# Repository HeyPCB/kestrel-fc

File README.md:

# Kestrel H7: FPV flight controller

**An STM32H743 flight controller for 5-inch 6S quads: two IMUs, a barometer, a 16 MB blackbox and its own 5 V and switchable 10 V BECs, on a 30.5 mm stack.**

The Kestrel H7 is the flight controller of [Kestrel](https://github.com/HeyPCB/kestrel), a 5-inch 6S FPV quad's electronics. Its pin map follows Betaflight's `MATEKH743` target wherever the functions match, so its timer and DMA assignments are proven ones; a Betaflight unified target and CLI defaults are in [`firmware/`](firmware/). The ICM-20602 flies Betaflight, and the BMI088 on its own SPI bus is there for INAV and ArduPilot.

| Layers | Size | Footprints (LCSC parts) | Nets | Connections routed | Routed vias | ERC errors / warnings | DRC errors / warnings / unconnected / parity | Parts per board, 10-board build |
|---|---|---|---|---|---|---|---|---|
| 6 | 40 x 40 mm | 114 (93) | 84 | 277 -> 0 open | 125 | 0 / 0 | 0 / 0 / 0 / 0 | $46.49 |

**Not fabricated, assembled, powered or flown yet.** Every number on this page is measured by KiCad
10.0.6 on the files in this repository ([`report.json`](report.json), [`fab/erc.json`](fab/erc.json),
[`fab/drc.json`](fab/drc.json)) or read from the live JLC/LCSC catalogue ([`bom_cost.md`](bom_cost.md):
parts only, at a 10-board build's price tier with JLC's Extended-part fee; the bare PCB and assembly are
quoted at order time).

| | |
|---|---|
| The whole drone: spec, build guide, BOM, measured results | [HeyPCB/kestrel](https://github.com/HeyPCB/kestrel) |
| KiCad 10 project | [`kicad/`](kicad/) |
| Gerbers, drill, BOM, CPL, STEP, schematic PDF | [`fab/`](fab/) |
| Firmware | [`firmware/betaflight/KESTRELH7/`](firmware/betaflight/KESTRELH7/): Betaflight unified target and CLI defaults |
| Renders | [front](media/top.png), [back](media/bottom.png), [hero](media/hero.png), [Circuit World thumbnail](media/circuit-world.png) |
| Brief and generator | [`design/`](design/) |

## What's on it

- **MCU:** STM32H743VIT6 (LQFP-100, 480 MHz, 2 MB flash), 8 MHz crystal, BOOT button, SWD pads.
- **IMUs:** ICM-20602 on SPI1 with its own interrupt (Betaflight's gyro); BMI088 on SPI4 (INAV and ArduPilot). Both run from their own AP2112K LDO, away from the BECs' switching.
- **Baro:** MS5611 on I2C1 at 0x77 (cover it with open-cell foam).
- **Blackbox:** W25Q128JV, 16 MB, on SPI3.
- **Power:** 2-6S from the ESC harness, SMAJ30A TVS, VBAT x 1/11 to an ADC; a 5 V BEC (LMR51430, 2 A budget) and a 10 V BEC for the VTX that PINIO1 switches off.
- **Ports:** JST-SH ESC 8-pin, VTX 6-pin, receiver 4-pin and GPS 6-pin; USB-C with USBLC6 ESD.
- **Pads:** M5-M8, UART1 and UART6, LED strip, buzzer, 5 V, 10 V, GND (the pad map is in the hub's [BUILD.md](https://github.com/HeyPCB/kestrel/blob/main/BUILD.md)).

## Ordering

6 layers, 1.6 mm, 1 oz copper; parts on both faces. Upload [`fab/kestrel_fc_gerbers.zip`](fab/kestrel_fc_gerbers.zip), [`fab/kestrel_fc_bom.csv`](fab/kestrel_fc_bom.csv)
and [`fab/kestrel_fc_cpl_jlc.csv`](fab/kestrel_fc_cpl_jlc.csv) to JLCPCB: every part has an LCSC number.
Bring-up, one board at a time, is in the hub's [BUILD.md](https://github.com/HeyPCB/kestrel/blob/main/BUILD.md).

## How it was made

Designed with the HeyPCB method on KiCad 10.0.6, headless, by the `heypcb-kicad` pipeline: a written brief composed from reusable circuit blocks, every pin from KiCad's own symbol library, every part bound to an LCSC number from a dated catalogue read, then ERC, a netlist round trip, locked placement, Freerouting 2.4.1, pours and stitching, silkscreen, DRC with schematic parity, DFM and a fab gate, each stage gated by a measurement. [`design/make_brief.py`](design/make_brief.py) regenerates the brief (outline, part locks, net
classes) from code.

Part of [Kestrel](https://github.com/HeyPCB/kestrel), a 5-inch 6S FPV quad's electronics.

## License

Hardware: [CERN-OHL-S v2](LICENSE). The Betaflight target in [`firmware/`](firmware/) is GPL-3.0 ([`firmware/LICENSE`](firmware/LICENSE)), the licence of the betaflight/config repository it builds in, whose `MATEKH743` timer and DMA assignments it reuses. KiCad's symbol, footprint and 3D libraries used in the
design are CC-BY-SA 4.0 with the KiCad library exception.

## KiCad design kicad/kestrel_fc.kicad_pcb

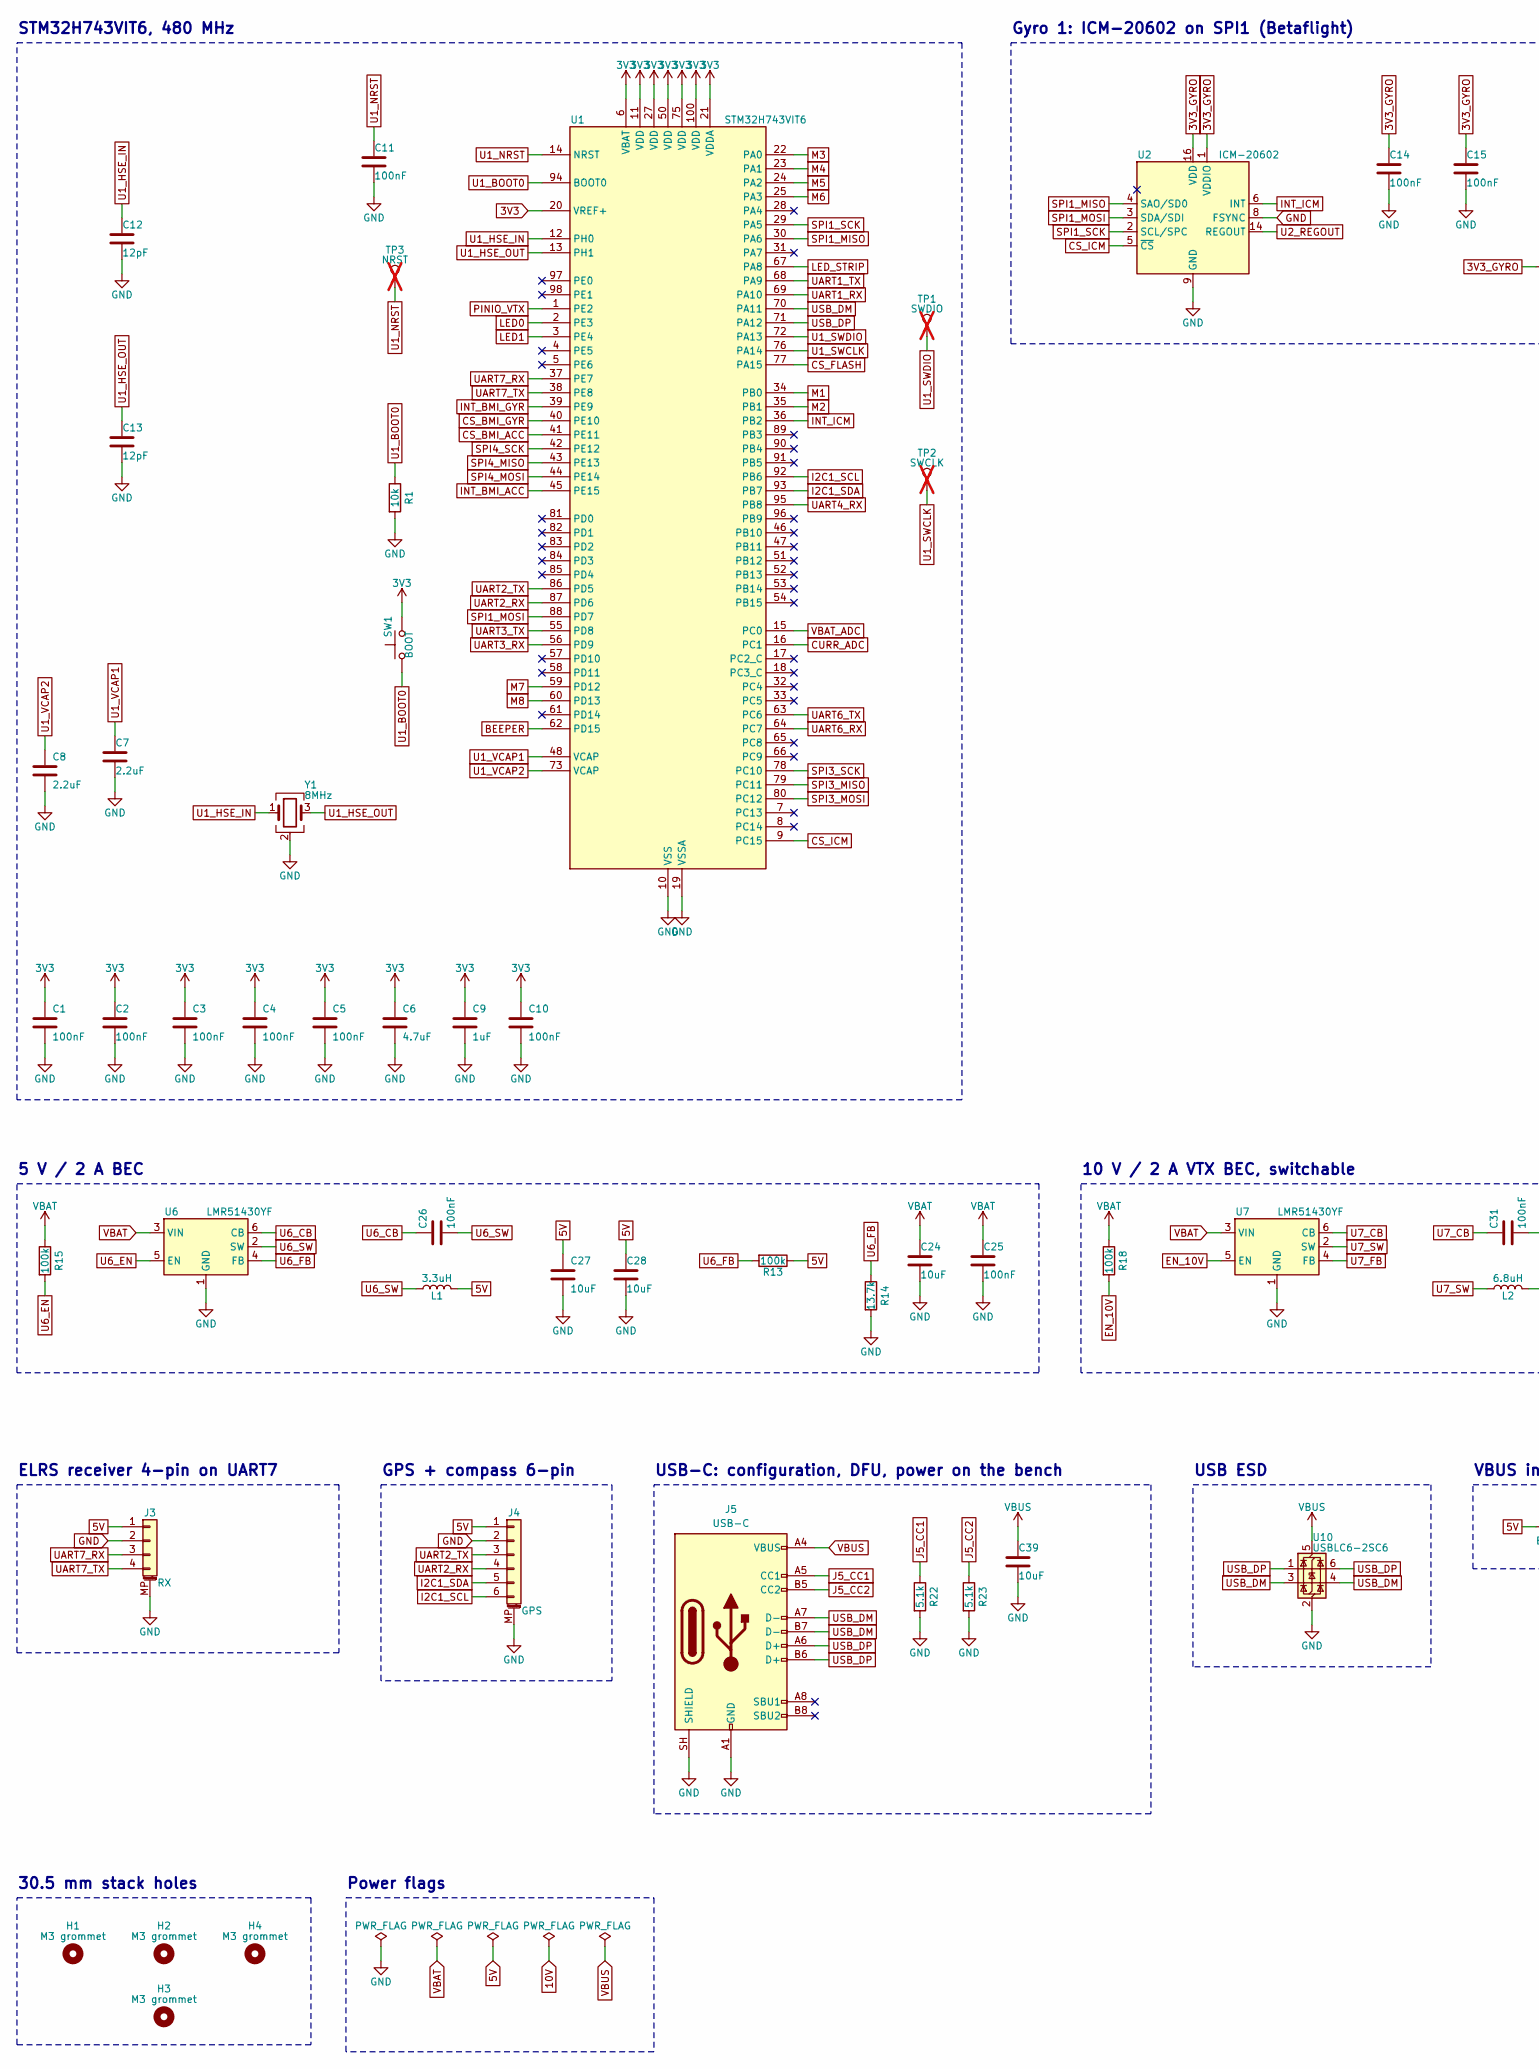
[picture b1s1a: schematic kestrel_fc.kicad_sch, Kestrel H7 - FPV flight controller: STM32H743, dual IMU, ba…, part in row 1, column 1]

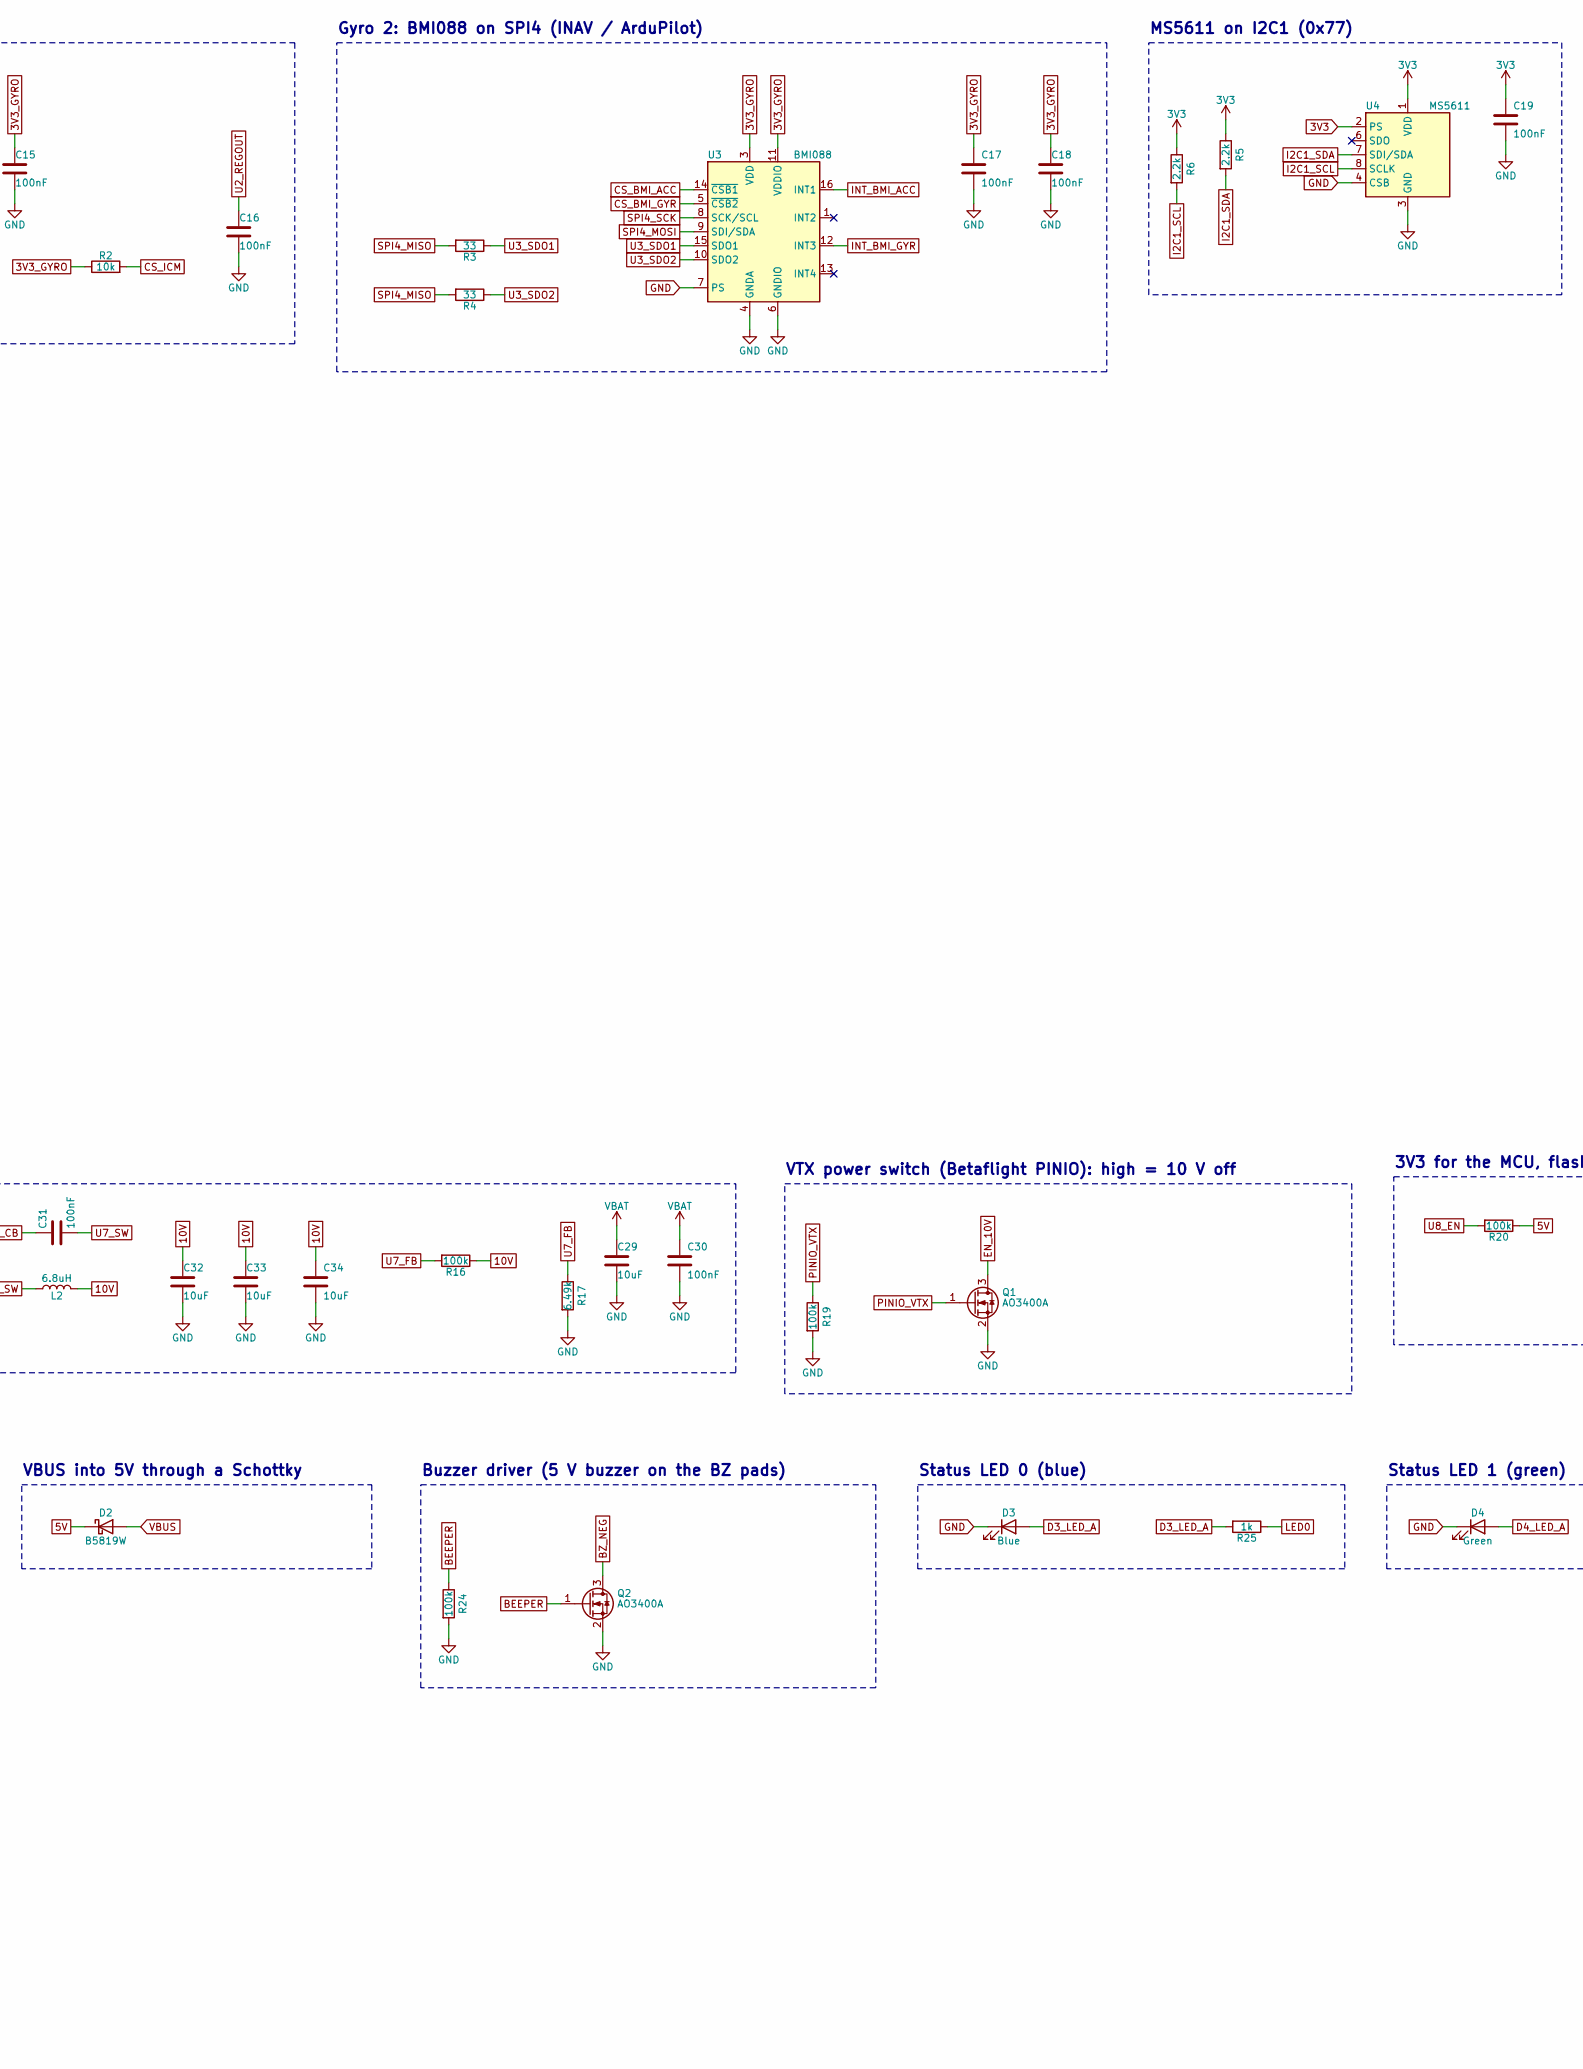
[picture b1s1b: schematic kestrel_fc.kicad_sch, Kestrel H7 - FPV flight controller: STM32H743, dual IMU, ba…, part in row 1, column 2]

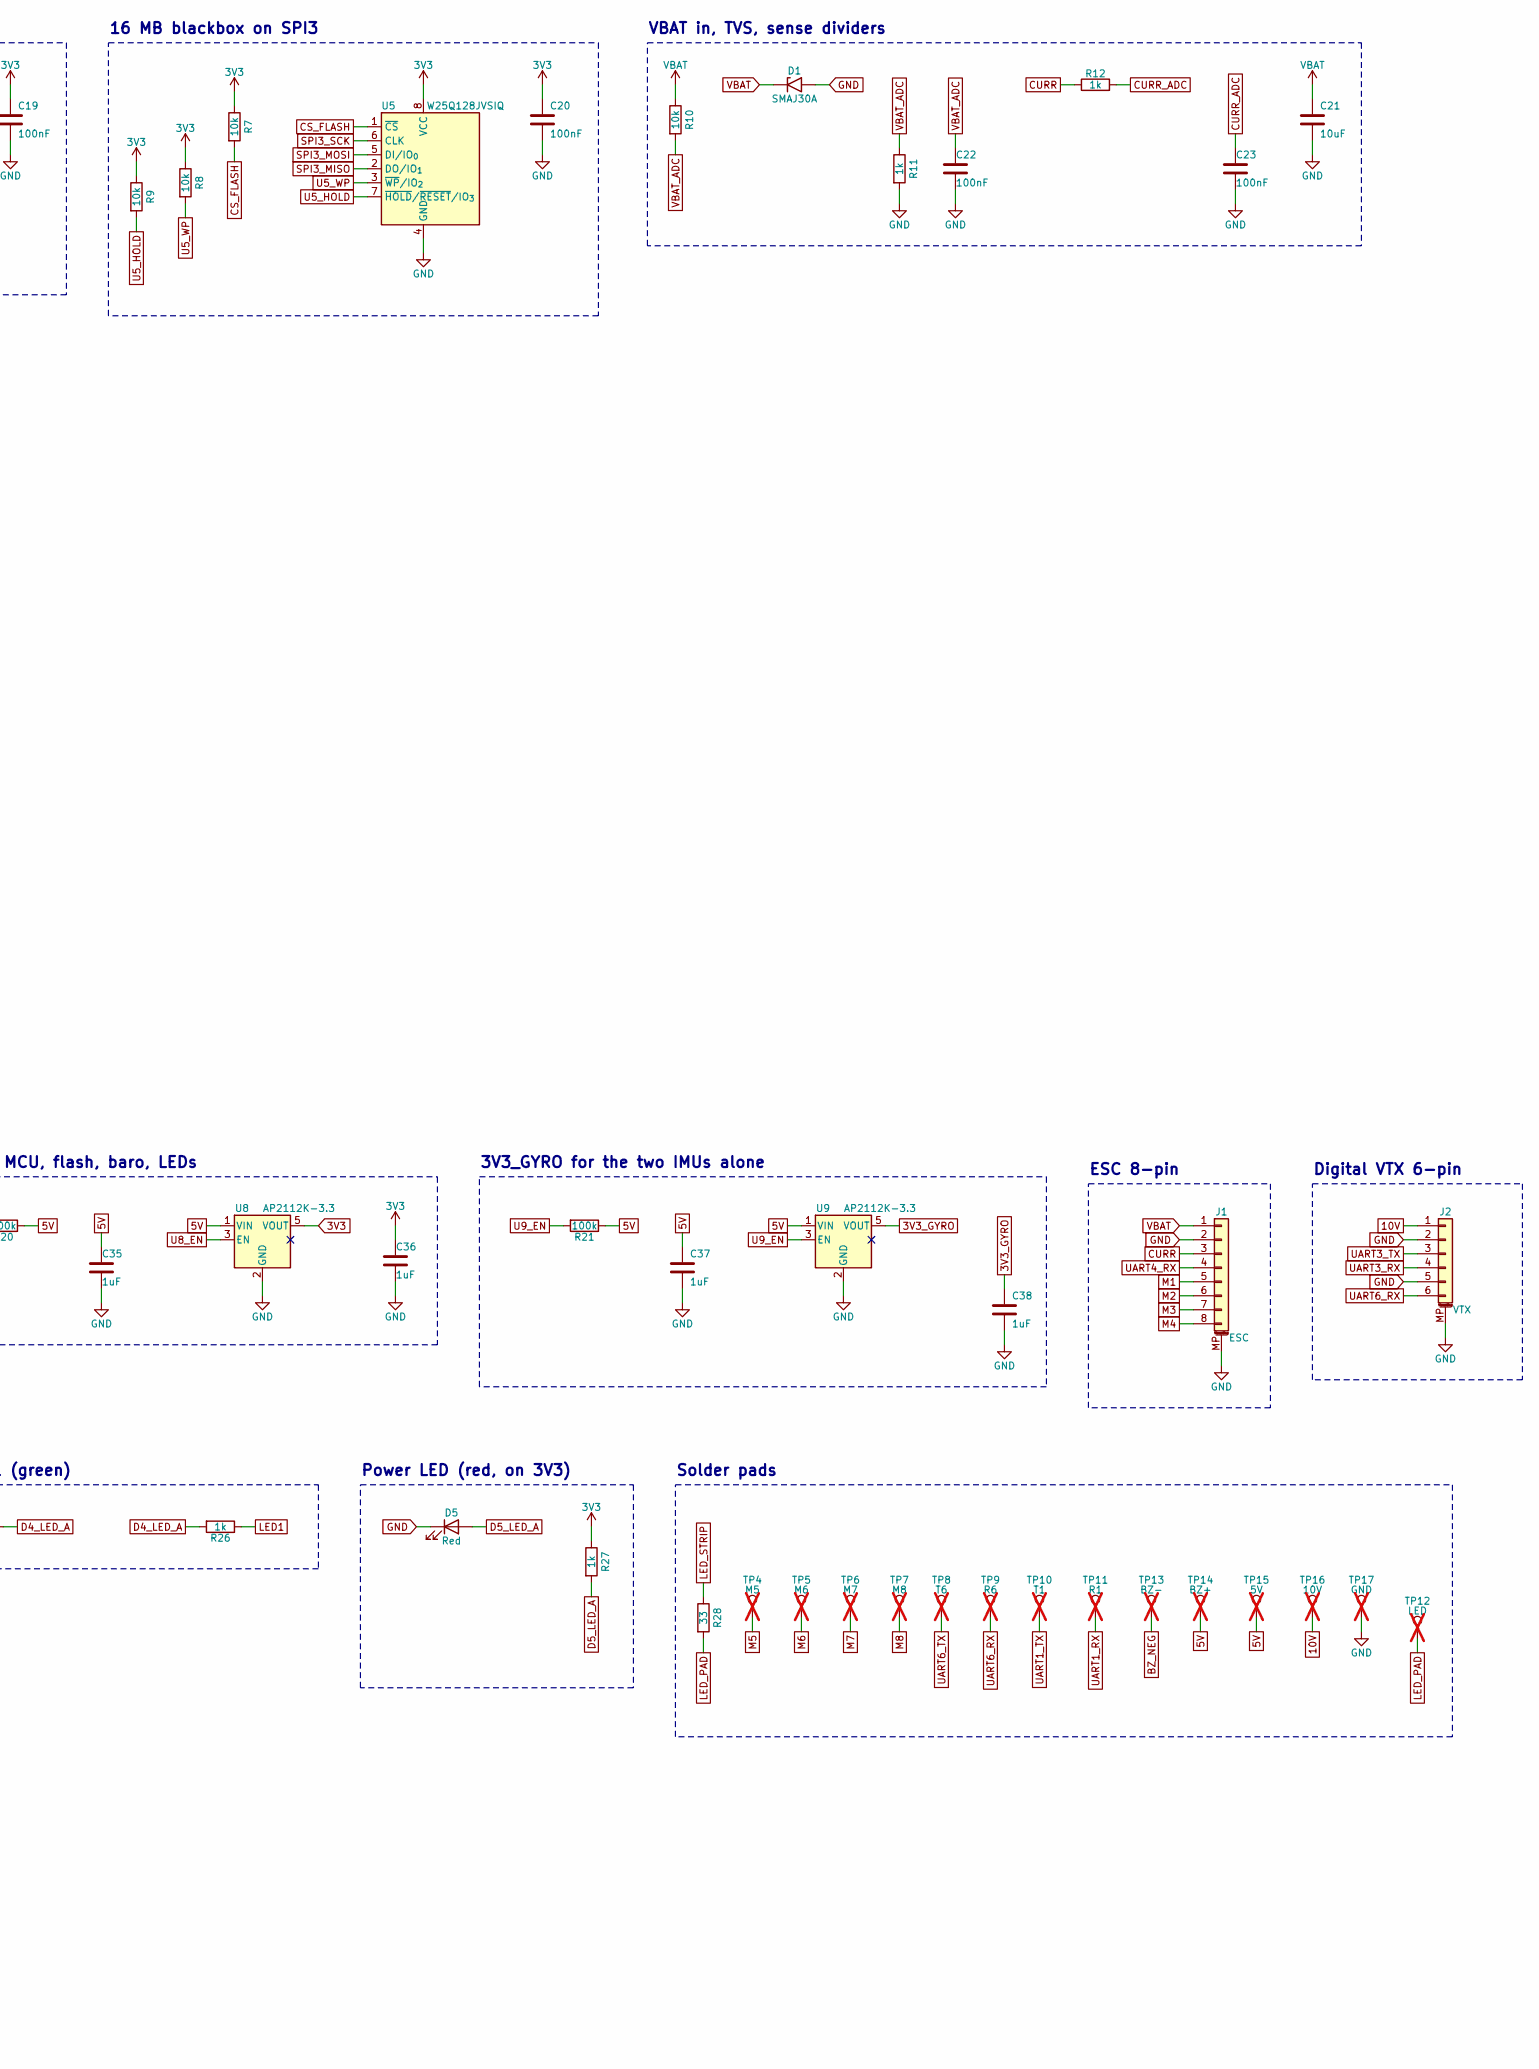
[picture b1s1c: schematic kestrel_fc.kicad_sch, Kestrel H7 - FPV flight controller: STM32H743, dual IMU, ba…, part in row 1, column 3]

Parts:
C1, C2, C3, C4, C5, C10, C11, C14, C15, C16, C17, C18, C19, C20, C22, C23, C26, C31: 100nF; C_0402_1005Metric; MPN CL05B104KO5NNNC; LCSC C1525
C6: 4.7uF; C_0603_1608Metric; MPN CL10A475KO8NNNC; LCSC C19666
C7, C8: 2.2uF; C_0402_1005Metric; MPN CL05A225MQ5NSNC; LCSC C12530
C9, C35, C36, C37, C38: 1uF; C_0402_1005Metric; MPN CL05A105KA5NQNC; LCSC C52923
C12, C13: 12pF; C_0603_1608Metric; MPN CL10C120JB8NNNC; LCSC C38523
C21, C24, C27, C28, C29, C32, C33, C34: 10uF; C_0805_2012Metric; MPN GRM21BR61H106KE43L; LCSC C440198
C25, C30: 100nF; C_0402_1005Metric; MPN CL05B104KB54PNC; LCSC C307331
C39: 10uF; C_0805_2012Metric; MPN CL21A106KAYNNNE; LCSC C15850
D1: SMAJ30A; D_SMA; MPN SMAJ30A; LCSC C908776
D2: B5819W; D_SOD-123; MPN B5819W SL; LCSC C8598
D3: Blue; LED_0603_1608Metric; MPN NCD0603B1; LCSC C84266
D4: Green; LED_0603_1608Metric; MPN KT-0603G; LCSC C12624
D5: Red; LED_0603_1608Metric; MPN KT-0603R; LCSC C2286
H1, H2, H3, H4: M3 grommet; MountingHole_4mm
J1: ESC; JST_SH_SM08B-SRSS-TB_1x08-1MP_P1.00mm_Horizontal; MPN SM08B-SRSS-TB(LF)(SN); LCSC C160407
J2: VTX; JST_SH_SM06B-SRSS-TB_1x06-1MP_P1.00mm_Horizontal; MPN SM06B-SRSS-TB(LF)(SN); LCSC C160405
J3: RX; JST_SH_SM04B-SRSS-TB_1x04-1MP_P1.00mm_Horizontal; MPN SM04B-SRSS-TB(LF)(SN); LCSC C160404
J4: GPS; JST_SH_SM06B-SRSS-TB_1x06-1MP_P1.00mm_Horizontal; MPN SM06B-SRSS-TB(LF)(SN); LCSC C160405
J5: USB-C; USB_C_Receptacle_HCTL_HC-TYPE-C-16P-01A; MPN HC-TYPE-C-16P-01A; LCSC C2894897
L1: 3.3uH; L_Sunlord_SWPA5040S; MPN SWPA5040S3R3MT; LCSC C14656
L2: 6.8uH; L_Sunlord_SWPA5040S; MPN SWPA5040S6R8MT; LCSC C36411
Q1, Q2: AO3400A; SOT-23; MPN AO3400A; LCSC C20917
R1, R2, R7, R8, R9, R10: 10k; R_0402_1005Metric; MPN 0402WGF1002TCE; LCSC C25744
R3, R4, R28: 33; R_0402_1005Metric; MPN 0402WGF330JTCE; LCSC C25105
R5, R6: 2.2k; R_0402_1005Metric; MPN 0402WGF2201TCE; LCSC C25879
R11, R12: 1k; R_0402_1005Metric; MPN 0402WGF1001TCE; LCSC C11702
R13, R15, R16, R18, R19, R24: 100k; R_0603_1608Metric; MPN 0603WAF1003T5E; LCSC C25803
R14: 13.7k; R_0603_1608Metric; MPN 0603WAF1372T5E; LCSC C22793
R17: 6.49k; R_0603_1608Metric; MPN 0603WAF6491T5E; LCSC C23088
R20, R21: 100k; R_0402_1005Metric; MPN 0402WGF1003TCE; LCSC C25741
R22, R23: 5.1k; R_0402_1005Metric; MPN 0402WGF5101TCE; LCSC C25905
R25, R26, R27: 1k; R_0603_1608Metric; MPN 0603WAF1001T5E; LCSC C21190
SW1: BOOT; SW_SPST_B3U-1000P; MPN B3U-1000P; LCSC C231329
TP1: SWDIO; TestPoint_Pad_1.0x1.0mm; not fitted
TP2: SWCLK; TestPoint_Pad_1.0x1.0mm; not fitted
TP3: NRST; TestPoint_Pad_1.0x1.0mm; not fitted
TP4: M5; TestPoint_Pad_1.5x1.5mm; not fitted
TP5: M6; TestPoint_Pad_1.5x1.5mm; not fitted
TP6: M7; TestPoint_Pad_1.5x1.5mm; not fitted
TP7: M8; TestPoint_Pad_1.5x1.5mm; not fitted
TP8: T6; TestPoint_Pad_1.5x1.5mm; not fitted
TP9: R6; TestPoint_Pad_1.5x1.5mm; not fitted
TP10: T1; TestPoint_Pad_1.5x1.5mm; not fitted
TP11: R1; TestPoint_Pad_1.5x1.5mm; not fitted
TP12: LED; TestPoint_Pad_1.5x1.5mm; not fitted
TP13: BZ-; TestPoint_Pad_1.5x1.5mm; not fitted
TP14: BZ+; TestPoint_Pad_1.5x1.5mm; not fitted
TP15: 5V; TestPoint_Pad_1.5x1.5mm; not fitted
TP16: 10V; TestPoint_Pad_1.5x1.5mm; not fitted
TP17: GND; TestPoint_Pad_1.5x1.5mm; not fitted
U1: STM32H743VIT6; LQFP-100_14x14mm_P0.5mm; MPN STM32H743VIT6; LCSC C114409
U2: ICM-20602; LGA-16_3x3mm_P0.5mm_LayoutBorder3x5y; MPN ICM-20602; LCSC C97633
U3: BMI088; Bosch_LGA-16_4.5x3mm_P0.5mm_LayoutBorder7x1y_ClockwisePinNu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; MPN BMI088; LCSC C194919
U4: MS5611; LGA-8_3x5mm_P1.25mm; MPN MS561101BA03-50; LCSC C15639
U5: W25Q128JVSIQ; SOIC-8_5.3x5.3mm_P1.27mm; MPN W25Q128JVSIQ; LCSC C97521
U6, U7: LMR51430YF; SOT-23-6; MPN LMR51430YFDDCR; LCSC C5219261
U8, U9: AP2112K-3.3; SOT-23-5; MPN AP2112K-3.3TRG1; LCSC C51118
U10: USBLC6-2SC6; SOT-23-6; MPN USBLC6-2SC6; LCSC C7519
Y1: 8MHz; Crystal_SMD_3225-4Pin_3.2x2.5mm; MPN TAXM8M4RDBCCT2T; LCSC C400090

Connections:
3V3: C1.1, C2.1, C3.1, C4.1, C5.1, C6.1, C9.1, C10.1, C19.1, C20.1, C36.1, R5.1, R6.1, R7.1, R8.1, R9.1, R27.1, SW1.2, U1.6 (VBAT), U1.11 (VDD), U1.20 (VREF+), U1.21 (VDDA), U1.27 (VDD), U1.50 (VDD), U1.75 (VDD), U1.100 (VDD), U4.1 (VDD), U4.2 (PS), U5.8 (VCC), U8.5 (VOUT)
3V3_GYRO: C14.1, C15.1, C17.1, C18.1, C38.1, R2.1, U2.1 (VDDIO), U2.16 (VDD), U3.3 (VDD), U3.11 (VDDIO), U9.5 (VOUT)
5V: C27.1, C28.1, C35.1, C37.1, D2.1 (K), J3.1, J4.1, L1.2, R13.1, R20.1, R21.1, TP14.1, TP15.1, U8.1 (VIN), U9.1 (VIN)
10V: C32.1, C33.1, C34.1, J2.1, L2.2, R16.1, TP16.1
BEEPER: Q2.1 (G), R24.1, U1.62 (PD15)
BZ_NEG: Q2.3 (D), TP13.1
CS_BMI_ACC: U1.41 (PE11), U3.14 (~CSB1)
CS_BMI_GYR: U1.40 (PE10), U3.5 (~CSB2)
CS_FLASH: R7.2, U1.77 (PA15), U5.1 (~CS)
CS_ICM: R2.2, U1.9 (PC15), U2.5 (~CS)
CURR: J1.3, R12.1
CURR_ADC: C23.1, R12.2, U1.16 (PC1)
D3_LED_A: D3.2 (A), R25.2
D4_LED_A: D4.2 (A), R26.2
D5_LED_A: D5.2 (A), R27.2
EN_10V: Q1.3 (D), R18.2, U7.5 (EN)
GND: C1.2, C2.2, C3.2, C4.2, C5.2, C6.2, C7.2, C8.2, C9.2, C10.2, C11.2, C12.2, C13.2, C14.2, C15.2, C16.2, C17.2, C18.2, C19.2, C20.2, C21.2, C22.2, C23.2, C24.2, C25.2, C27.2, C28.2, C29.2, C30.2, C32.2, C33.2, C34.2, C35.2, C36.2, C37.2, C38.2, C39.2, D1.2 (A2), D3.1 (K), D4.1 (K), D5.1 (K), J1.2, J1.MP (MountPin), J2.2, J2.5, J2.MP (MountPin), J3.2, J3.MP (MountPin), J4.2, J4.MP (MountPin), J5.A1 (GND), J5.A12 (GND), J5.B1 (GND), J5.B12 (GND), J5.SH (SHIELD), Q1.2 (S), Q2.2 (S), R1.2, R11.2, R14.2, R17.2, R19.2, R22.2, R23.2, R24.2, TP17.1, U1.10 (VSS), U1.19 (VSSA), U1.26 (VSS), U1.49 (VSS), U1.74 (VSS), U1.99 (VSS), U2.8 (FSYNC), U2.9 (GND), U2.10 (GND), U2.11 (GND), U2.12 (GND), U2.13 (GND), U2.15 (GND), U3.2 (GNDA), U3.4 (GNDA), U3.6 (GNDIO), U3.7 (PS), U4.3 (GND), U4.4 (CSB), U4.5 (CSB), U5.4 (GND), U6.1 (GND), U7.1 (GND), U8.2 (GND), U9.2 (GND), U10.2 (GND), Y1.2 (G), Y1.4 (G)
I2C1_SCL: J4.6, R6.2, U1.92 (PB6), U4.8 (SCLK)
I2C1_SDA: J4.5, R5.2, U1.93 (PB7), U4.7 (SDI/SDA)
INT_BMI_ACC: U1.45 (PE15), U3.16 (INT1)
INT_BMI_GYR: U1.39 (PE9), U3.12 (INT3)
INT_ICM: U1.36 (PB2), U2.6 (INT)
J5_CC1: J5.A5 (CC1), R22.1
J5_CC2: J5.B5 (CC2), R23.1
LED0: R25.1, U1.2 (PE3)
LED1: R26.1, U1.3 (PE4)
LED_PAD: R28.2, TP12.1
LED_STRIP: R28.1, U1.67 (PA8)
M1: J1.5, U1.34 (PB0)
M2: J1.6, U1.35 (PB1)
M3: J1.7, U1.22 (PA0)
M4: J1.8, U1.23 (PA1)
M5: TP4.1, U1.24 (PA2)
M6: TP5.1, U1.25 (PA3)
M7: TP6.1, U1.59 (PD12)
M8: TP7.1, U1.60 (PD13)
PINIO_VTX: Q1.1 (G), R19.1, U1.1 (PE2)
SPI1_MISO: U1.30 (PA6), U2.4 (SAO/SD0)
SPI1_MOSI: U1.88 (PD7), U2.3 (SDA/SDI)
SPI1_SCK: U1.29 (PA5), U2.2 (SCL/SPC)
SPI3_MISO: U1.79 (PC11), U5.2 (DO/IO_{1})
SPI3_MOSI: U1.80 (PC12), U5.5 (DI/IO_{0})
SPI3_SCK: U1.78 (PC10), U5.6 (CLK)
SPI4_MISO: R3.2, R4.2, U1.43 (PE13)
SPI4_MOSI: U1.44 (PE14), U3.9 (SDI/SDA)
SPI4_SCK: U1.42 (PE12), U3.8 (SCK/SCL)
U1_BOOT0: R1.1, SW1.1, U1.94 (BOOT0)
U1_HSE_IN: C12.1, U1.12 (PH0), Y1.1
U1_HSE_OUT: C13.1, U1.13 (PH1), Y1.3
U1_NRST: C11.1, TP3.1, U1.14 (NRST)
U1_SWCLK: TP2.1, U1.76 (PA14)
U1_SWDIO: TP1.1, U1.72 (PA13)
U1_VCAP1: C7.1, U1.48 (VCAP)
U1_VCAP2: C8.1, U1.73 (VCAP)
U2_REGOUT: C16.1, U2.14 (REGOUT)
U3_SDO1: R3.1, U3.15 (SDO1)
U3_SDO2: R4.1, U3.10 (SDO2)
U5_HOLD: R9.2, U5.7 (~HOLD/~RESET/IO_{3})
U5_WP: R8.2, U5.3 (~WP/IO_{2})
U6_CB: C26.1, U6.6 (CB)
U6_EN: R15.2, U6.5 (EN)
U6_FB: R13.2, R14.1, U6.4 (FB)
U6_SW: C26.2, L1.1, U6.2 (SW)
U7_CB: C31.1, U7.6 (CB)
U7_FB: R16.2, R17.1, U7.4 (FB)
U7_SW: C31.2, L2.1, U7.2 (SW)
U8_EN: R20.2, U8.3 (EN)
U9_EN: R21.2, U9.3 (EN)
UART1_RX: TP11.1, U1.69 (PA10)
UART1_TX: TP10.1, U1.68 (PA9)
UART2_RX: J4.4, U1.87 (PD6)
UART2_TX: J4.3, U1.86 (PD5)
UART3_RX: J2.4, U1.56 (PD9)
UART3_TX: J2.3, U1.55 (PD8)
UART4_RX: J1.4, U1.95 (PB8)
UART6_RX: J2.6, TP9.1, U1.64 (PC7)
UART6_TX: TP8.1, U1.63 (PC6)
UART7_RX: J3.3, U1.37 (PE7)
UART7_TX: J3.4, U1.38 (PE8)
USB_DM: J5.A7 (D-), J5.B7 (D-), U1.70 (PA11), U10.3 (I/O2), U10.4 (I/O2)
USB_DP: J5.A6 (D+), J5.B6 (D+), U1.71 (PA12), U10.1 (I/O1), U10.6 (I/O1)
VBAT: C21.1, C24.1, C25.1, C29.1, C30.1, D1.1 (A1), J1.1, R10.1, R15.1, R18.1, U6.3 (VIN), U7.3 (VIN)
VBAT_ADC: C22.1, R10.2, R11.1, U1.15 (PC0)
VBUS: C39.1, D2.2 (A), J5.A4 (VBUS), J5.A9 (VBUS), J5.B4 (VBUS), J5.B9 (VBUS), U10.5 (VBUS)

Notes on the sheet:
STM32H743VIT6, 480 MHz
Gyro 1: ICM-20602 on SPI1 (Betaflight)
Gyro 2: BMI088 on SPI4 (INAV / ArduPilot)
MS5611 on I2C1 (0x77)
16 MB blackbox on SPI3
VBAT in, TVS, sense dividers
5 V / 2 A BEC
10 V / 2 A VTX BEC, switchable
VTX power switch (Betaflight PINIO): high = 10 V off
3V3 for the MCU, flash, baro, LEDs
3V3_GYRO for the two IMUs alone
ESC 8-pin
Digital VTX 6-pin
ELRS receiver 4-pin on UART7
GPS + compass 6-pin
USB-C: configuration, DFU, power on the bench
USB ESD
VBUS into 5V through a Schottky
Buzzer driver (5 V buzzer on the BZ pads)
Status LED 0 (blue)
Status LED 1 (green)
Power LED (red, on 3V3)
Solder pads
30.5 mm stack holes
Power flags

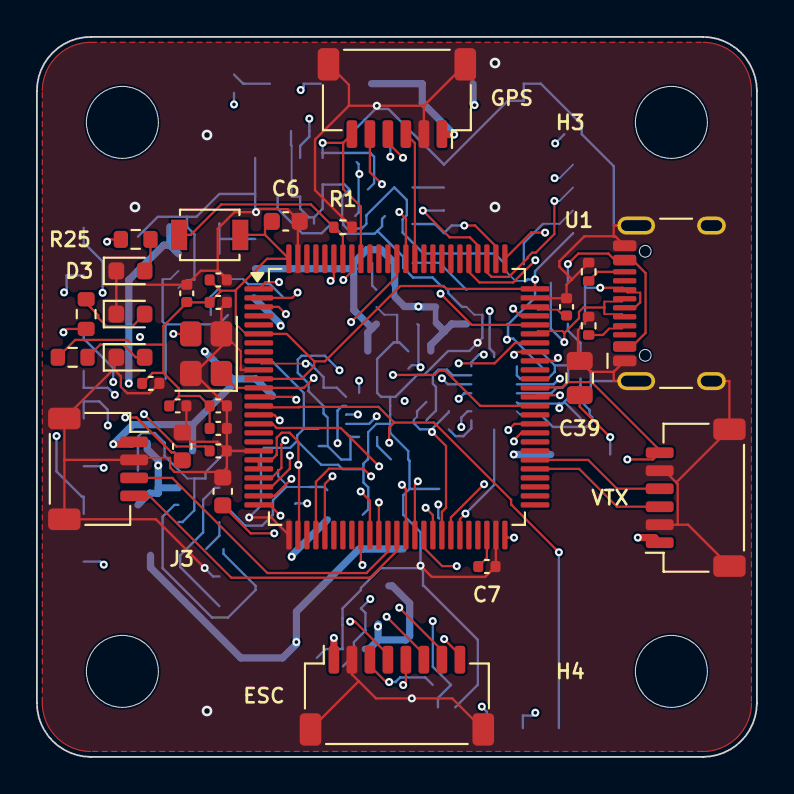
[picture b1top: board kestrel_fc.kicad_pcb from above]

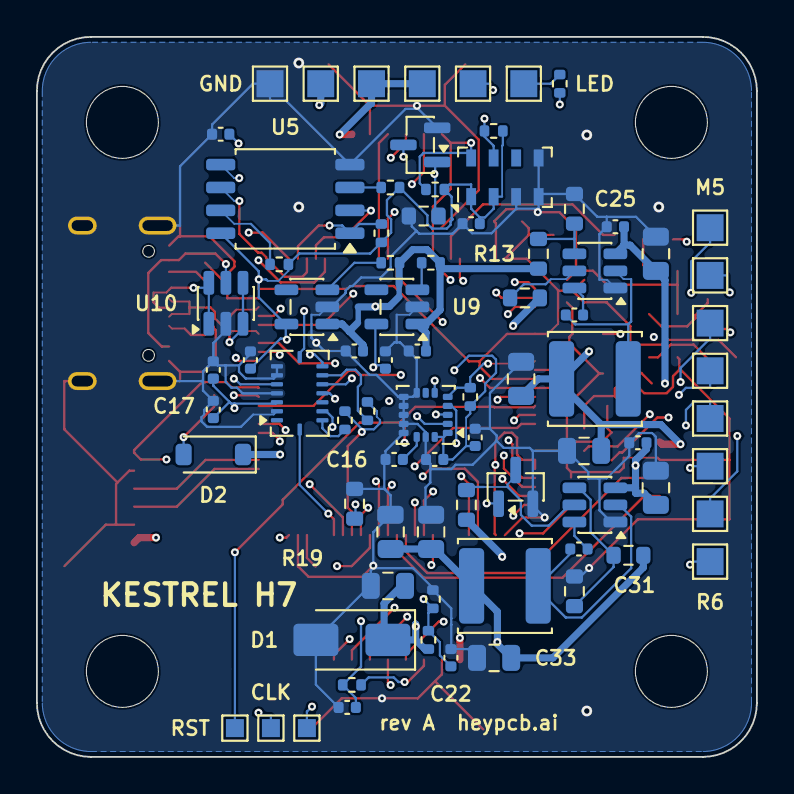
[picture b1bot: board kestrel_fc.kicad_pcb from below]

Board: 6 copper layers, 40.0 x 40.0 mm, 114 parts (79 on the bottom side), 84 nets.

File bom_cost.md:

| Refs | Value | Qty | LCSC | MPN | Class | Unit @10 | Line |
|---|---|---|---|---|---|---|---|
| C1,C2,C3,C4,C5,C10,C11,C14,C15,C16,C17,C18,C19,C20,C22,C23,C26,C31 | 100nF | 18 | C1525 | CL05B104KO5NNNC | basic | $0.0060 | $0.1080 |
| C6 | 4.7uF | 1 | C19666 | CL10A475KO8NNNC | basic | $0.0236 | $0.0236 |
| C7,C8 | 2.2uF | 2 | C12530 | CL05A225MQ5NSNC | basic | $0.0078 | $0.0156 |
| C9,C35,C36,C37,C38 | 1uF | 5 | C52923 | CL05A105KA5NQNC | basic | $0.0143 | $0.0715 |
| C12,C13 | 12pF | 2 | C38523 | CL10C120JB8NNNC | basic | $0.0081 | $0.0162 |
| C21,C24,C27,C28,C29,C32,C33,C34 | 10uF | 8 | C440198 | GRM21BR61H106KE43L | basic | $0.2473 | $1.9784 |
| C25,C30 | 100nF | 2 | C307331 | CL05B104KB54PNC | basic | $0.0076 | $0.0152 |
| C39 | 10uF | 1 | C15850 | CL21A106KAYNNNE | basic | $0.0773 | $0.0773 |
| D1 | SMAJ30A | 1 | C908776 | SMAJ30A | extended | $0.0349 | $0.0349 |
| D2 | B5819W | 1 | C8598 | B5819W SL | basic | $0.0261 | $0.0261 |
| D3 | Blue | 1 | C84266 | NCD0603B1 | extended | $0.0170 | $0.0170 |
| D4 | Green | 1 | C12624 | KT-0603G | extended | $0.0122 | $0.0122 |
| D5 | Red | 1 | C2286 | KT-0603R | basic | $0.0073 | $0.0073 |
| J1 | ESC | 1 | C160407 | SM08B-SRSS-TB(LF)(SN) | extended | $0.3188 | $0.3188 |
| J2 | VTX | 1 | C160405 | SM06B-SRSS-TB(LF)(SN) | extended | $0.3020 | $0.3020 |
| J3 | RX | 1 | C160404 | SM04B-SRSS-TB(LF)(SN) | extended | $0.2262 | $0.2262 |
| J4 | GPS | 1 | C160405 | SM06B-SRSS-TB(LF)(SN) | extended | $0.3020 | $0.3020 |
| J5 | USB-C | 1 | C2894897 | HC-TYPE-C-16P-01A | extended | $0.0998 | $0.0998 |
| L1 | 3.3uH | 1 | C14656 | SWPA5040S3R3MT | extended | $0.0783 | $0.0783 |
| L2 | 6.8uH | 1 | C36411 | SWPA5040S6R8MT | extended | $0.0803 | $0.0803 |
| Q1,Q2 | AO3400A | 2 | C20917 | AO3400A | basic | $0.0846 | $0.1692 |
| R1,R2,R7,R8,R9,R10 | 10k | 6 | C25744 | 0402WGF1002TCE | basic | $0.0029 | $0.0174 |
| R3,R4,R28 | 33 | 3 | C25105 | 0402WGF330JTCE | basic | $0.0010 | $0.0030 |
| R5,R6 | 2.2k | 2 | C25879 | 0402WGF2201TCE | basic | $0.0010 | $0.0020 |
| R11,R12 | 1k | 2 | C11702 | 0402WGF1001TCE | basic | $0.0011 | $0.0022 |
| R13,R15,R16,R18,R19,R24 | 100k | 6 | C25803 | 0603WAF1003T5E | basic | $0.0016 | $0.0096 |
| R14 | 13.7k | 1 | C22793 | 0603WAF1372T5E | extended | $0.0021 | $0.0021 |
| R17 | 6.49k | 1 | C23088 | 0603WAF6491T5E | extended | $0.0013 | $0.0013 |
| R20,R21 | 100k | 2 | C25741 | 0402WGF1003TCE | basic | $0.0040 | $0.0080 |
| R22,R23 | 5.1k | 2 | C25905 | 0402WGF5101TCE | basic | $0.0009 | $0.0018 |
| R25,R26,R27 | 1k | 3 | C21190 | 0603WAF1001T5E | basic | $0.0039 | $0.0117 |
| SW1 | BOOT | 1 | C231329 | B3U-1000P | extended | $0.1784 | $0.1784 |
| U1 | STM32H743VIT6 | 1 | C114409 | STM32H743VIT6 | extended | $8.3101 | $8.3101 |
| U2 | ICM-20602 | 1 | C97633 | ICM-20602 | extended | $6.2635 | $6.2635 |
| U3 | BMI088 | 1 | C194919 | BMI088 | extended | $11.3230 | $11.3230 |
| U4 | MS5611 | 1 | C15639 | MS561101BA03-50 | extended | $6.2798 | $6.2798 |
| U5 | W25Q128JVSIQ | 1 | C97521 | W25Q128JVSIQ | basic | $2.1231 | $2.1231 |
| U6,U7 | LMR51430YF | 2 | C5219261 | LMR51430YFDDCR | extended | $0.6718 | $1.3436 |
| U8,U9 | AP2112K-3.3 | 2 | C51118 | AP2112K-3.3TRG1 | extended | $0.1577 | $0.3154 |
| U10 | USBLC6-2SC6 | 1 | C7519 | USBLC6-2SC6 | extended | $0.1639 | $0.1639 |
| Y1 | 8MHz | 1 | C400090 | TAXM8M4RDBCCT2T | extended | $0.1458 | $0.1458 |
| | **Parts** | | | | | | **$40.49** |
| | Extended-part loading fee ($3 x 20 / 10 boards) | | | | | | $6.00 |
| | **BOM per board @10** | | | | | | **$46.49** |

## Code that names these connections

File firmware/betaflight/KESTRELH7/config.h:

/*
 * Kestrel H7 - Betaflight unified target (config.h for the betaflight/config repository, 4.5+).
 *
 * Every pin below is the net the board's brief puts on that MCU pin (design/make_brief.py,
 * MCU_PINS), named from the KiCad 10 MCU_ST_STM32H7:STM32H743VITx symbol. The motor, LED-strip, UART,
 * I2C1, SPI1, SPI4 and ADC pins are the ones MATEKH743 ships with (configs/MTKS/MATEKH743/config.h,
 * read 2026-10-05), so their timer and DMA assignments below are that target's, unchanged.
 *
 * Not in Betaflight: the BMI088 (gyro 2, SPI4, CS PE11 / PE10) has no Betaflight driver; it is the
 * second IMU for INAV and ArduPilot. Betaflight flies on the ICM-20602 alone.
 *
 * Build:  make CONFIG=KESTRELH7   (with this directory copied to configs/KESTRELH7 of betaflight/config)
 */

#pragma once

#define FC_TARGET_MCU     STM32H743

#define BOARD_NAME        KESTRELH7
#define MANUFACTURER_ID   HYPB

#define USE_ACC
#define USE_ACC_SPI_MPU6500         // ICM-20602 is read by the MPU6500 driver family
#define USE_GYRO
#define USE_GYRO_SPI_MPU6500
#define USE_BARO
#define USE_BARO_MS5611           // I2C1 at 0x77
#define USE_MAG
#define USE_MAG_LIS3MDL             // Kestrel GPS board's compass, I2C1 at 0x1E
#define USE_FLASH
#define USE_FLASH_W25Q128FV
#define USE_GPS

#define BEEPER_PIN           PD15
#define MOTOR1_PIN           PB0
#define MOTOR2_PIN           PB1
#define MOTOR3_PIN           PA0
#define MOTOR4_PIN           PA1
#define MOTOR5_PIN           PA2
#define MOTOR6_PIN           PA3
#define MOTOR7_PIN           PD12
#define MOTOR8_PIN           PD13
#define LED_STRIP_PIN        PA8
#define UART1_TX_PIN         PA9
#define UART2_TX_PIN         PD5
#define UART3_TX_PIN         PD8
#define UART6_TX_PIN         PC6
#define UART7_TX_PIN         PE8
#define UART1_RX_PIN         PA10
#define UART2_RX_PIN         PD6
#define UART3_RX_PIN         PD9
#define UART4_RX_PIN         PB8      // ESC telemetry in (the 4-in-1's TLM wire)
#define UART6_RX_PIN         PC7
#define UART7_RX_PIN         PE7
#define I2C1_SCL_PIN         PB6
#define I2C1_SDA_PIN         PB7
#define LED0_PIN             PE3
#define LED1_PIN             PE4
#define SPI1_SCK_PIN         PA5
#define SPI3_SCK_PIN         PC10
#define SPI4_SCK_PIN         PE12
#define SPI1_SDI_PIN         PA6
#define SPI3_SDI_PIN         PC11
#define SPI4_SDI_PIN         PE13
#define SPI1_SDO_PIN         PD7
#define SPI3_SDO_PIN         PC12
#define SPI4_SDO_PIN         PE14
#define ADC_VBAT_PIN         PC0
#define ADC_CURR_PIN         PC1
#define PINIO1_PIN           PE2      // high switches the 10 V VTX rail off
#define FLASH_CS_PIN         PA15
#define GYRO_1_EXTI_PIN      PB2
#define GYRO_1_CS_PIN        PC15

#define TIMER_PIN_MAPPING \
    TIMER_PIN_MAP( 0, PB0 , 2,  0) \
    TIMER_PIN_MAP( 1, PB1 , 2,  1) \
    TIMER_PIN_MAP( 2, PA0 , 2,  2) \
    TIMER_PIN_MAP( 3, PA1 , 2,  3) \
    TIMER_PIN_MAP( 4, PA2 , 2,  4) \
    TIMER_PIN_MAP( 5, PA3 , 2,  5) \
    TIMER_PIN_MAP( 6, PD12, 1,  6) \
    TIMER_PIN_MAP( 7, PD13, 1,  7) \
    TIMER_PIN_MAP( 8, PA8 , 1,  8)

#define ADC1_DMA_OPT        9
#define TIMUP3_DMA_OPT      11
#define TIMUP4_DMA_OPT      12
#define TIMUP5_DMA_OPT      13

#define BARO_I2C_INSTANCE   I2CDEV_1
#define MAG_I2C_INSTANCE    I2CDEV_1

#define DEFAULT_RX_FEATURE  FEATURE_RX_SERIAL
#define SERIALRX_UART       SERIAL_PORT_UART7      // the RX port: an ELRS receiver, CRSF

#define DEFAULT_BLACKBOX_DEVICE      BLACKBOX_DEVICE_FLASH
#define DEFAULT_CURRENT_METER_SOURCE CURRENT_METER_ADC
#define DEFAULT_VOLTAGE_METER_SOURCE VOLTAGE_METER_ADC
#define DEFAULT_CURRENT_METER_SCALE  125   // Kestrel 4in1: INA180A2 x 0.25 mOhm = 12.5 mV/A
#define DEFAULT_VOLTAGE_METER_SCALE  110   // 10k / 1k divider
#define BEEPER_INVERTED                    // an AO3400A low-side switch: the pin high sounds it

#define FLASH_SPI_INSTANCE  SPI3
#define PINIO1_BOX          40
#define GYRO_1_SPI_INSTANCE SPI1
// The ICM-20602 sits on the bottom face (its Z axis points down). Derived from the footprint, not yet
// measured on a board: check the Configurator's Setup tab before the first flight and correct with
// "set gyro_1_sensor_align" if the model does not follow the quad.
#define GYRO_1_ALIGN        CW0_DEG_FLIP

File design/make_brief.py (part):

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HOLE = 15.25                     # 30.5 mm pattern

MCU_PINS = {
    "U?.1": "PINIO_VTX", "U?.2": "LED0", "U?.3": "LED1", "U?.9": "CS_ICM",
    "U?.15": "VBAT_ADC", "U?.16": "CURR_ADC",
    "U?.22": "M3", "U?.23": "M4", "U?.24": "M5", "U?.25": "M6",
    "U?.29": "SPI1_SCK", "U?.30": "SPI1_MISO", "U?.88": "SPI1_MOSI", "U?.36": "INT_ICM",
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    {"block": "kestrel_bec_10v", "as": "bec10", "title": "10 V / 2 A VTX BEC, switchable",
     "nets": {"VIN": "VBAT", "VOUT": "10V", "EN": "EN_10V"}},
    {"block": "merch_lowside_fet", "as": "vtxsw", "title": "VTX power switch (Betaflight PINIO): high = 10 V off",
     "nets": {"LOAD": "EN_10V", "EN": "PINIO_VTX"}},
    {"block": "kestrel_ldo_3v3", "as": "ldo", "title": "3V3 for the MCU, flash, baro, LEDs", "nets": {"VIN": "5V", "VOUT": "3V3"}},
    {"block": "kestrel_ldo_3v3", "as": "ldog", "title": "3V3_GYRO for the two IMUs alone", "nets": {"VIN": "5V", "VOUT": "3V3_GYRO"}},
    {"block": "kestrel_esc_port", "as": "esc", "title": "ESC 8-pin",
     "nets": {"VBAT": "VBAT", "CURR": "CURR", "TLM": "UART4_RX", "M1": "M1", "M2": "M2", "M3": "M3", "M4": "M4"}},
    {"block": "kestrel_vtx_port", "as": "vtx", "title": "Digital VTX 6-pin",
     "nets": {"PWR": "10V", "TX": "UART3_TX", "RX": "UART3_RX", "SBUS": "UART6_RX"}},
    {"block": "kestrel_rx_port", "as": "rx", "title": "ELRS receiver 4-pin on UART7", "nets": {"5V": "5V", "RX": "UART7_RX", "TX": "UART7_TX"}},
    {"block": "kestrel_gps_port", "as": "gps", "title": "GPS + compass 6-pin",
     "nets": {"5V": "5V", "TX": "UART2_TX", "RX": "UART2_RX", "SDA": "I2C1_SDA", "SCL": "I2C1_SCL"}},
    {"block": "kestrel_usb_c", "as": "usb", "title": "USB-C: configuration, DFU, power on the bench",
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    {"block": "kestrel_usb_power", "as": "usbpwr", "title": "VBUS into 5V through a Schottky"},
    {"block": "merch_lowside_fet", "as": "buz", "title": "Buzzer driver (5 V buzzer on the BZ pads)",
     "nets": {"LOAD": "BZ_NEG", "EN": "BEEPER"}},
    {"block": "gpio_led", "as": "led0", "title": "Status LED 0 (blue)", "nets": {"SIG": "LED0"}, "values": {"D?": "Blue", "R?": "1k"}},
    {"block": "gpio_led", "as": "led1", "title": "Status LED 1 (green)", "nets": {"SIG": "LED1"}, "values": {"D?": "Green", "R?": "1k"}},
    {"block": "gpio_led", "as": "ledp", "title": "Power LED (red, on 3V3)", "nets": {"SIG": "3V3"}, "values": {"D?": "Red", "R?": "1k"}},
    {"block": "kestrel_aux_pads", "as": "pads", "title": "Solder pads",
     "nets": {"M5": "M5", "M6": "M6", "M7": "M7", "M8": "M8", "UART6_TX": "UART6_TX", "UART6_RX": "UART6_RX",
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           overhang=True)
# top face
L.lock("mcu:U?", CX, CY, 0, "MCU in the middle; its four pin sides face their ports")
L.lock("gps:J?", CX, 3.4, 180, "GPS port on the top edge, beside PD5/PD6 and PB6/PB7", overhang=True)
L.lock("usb:J?", W - 3.6, 14.8, 90, "USB-C on the right edge, beside PA11/PA12", overhang=True)
L.lock("rx:J?", 3.4, 24.0, 270, "receiver port on the left edge (UART7)", overhang=True)
L.lock("esc:J?", CX, H - 3.4, 0, "ESC port in the middle of the bottom edge, motors 1-2 above it", overhang=True)
L.lock("vtx:J?", W - 3.4, 25.6, 90, "VTX port on the right edge under the USB, beside PD8/PD9", overhang=True)
L.lock("mcu:Y?", 9.4, 17.6, 90, "8 MHz crystal at PH0/PH1")
L.lock("mcu:SW?", 9.6, 11.0, 0, "BOOT button")
L.lock("esd:U?", 29.5, 14.8, 90, "USB ESD behind the receptacle", side="bottom")
# bottom face
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             "second IMU for INAV and ArduPilot), both on their own 3.3 V LDO; MS5611 barometer on I2C1; "
             "W25Q128 16 MB blackbox on SPI3. Power from the ESC harness (2-6S, SMAJ30A TVS): LMR51430 BECs for "
             "5 V / 2 A and a switchable 10 V / 2 A for a digital VTX (Betaflight PINIO). JST-SH ports for a "
             "4-in-1 ESC (8-pin: VBAT, GND, CURR, TLM, M1-M4), a DJI O3 / Walksnail / HDZero VTX (6-pin), an "
             "ELRS receiver (4-pin) and a GPS + compass (6-pin); USB-C for configuration and DFU; pads for "
             "motors 5-8, two spare UARTs, an LED strip and a buzzer. Pin map after the MATEKH743 target.",
    "blocks": BLOCKS,
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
